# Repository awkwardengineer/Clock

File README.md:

# Intro
This is the repository for the AWK-105 Voltmeter clock. Here is where we'll be storing requirements documents, design history files, useful tidbits of information, and other material that otherwise wouldn't be release to manufacture or included in a Bill of Materials

##Consumer Facing Page
The repo may be cool, but it's not for everyone. The consumer facing product page has the bulk of the media material.

[Awkward Engineer Product Page](http://www.awkwardengineer.com/pages/voltmeter-clock)

##How This Repo Is Organized
In general, there are two categories of thing:  
+ Artifacts that will become part of the Bill Of Materials and will be released to a manufacturer. This includes CAD files, drawings, Gerbers, etc.  
+ Documentation and design files that record useful and important information, but that the manufacturer doesn't need to actually MAKE something.

The idea was to try to organize the documentation near the design file, kindof like things are arranged below.

Clock  
|  
|--Mechanical  
|&nbsp;&nbsp;&nbsp;|----CAD            <=== BOM artifacts, 3d part files, drawings  
|&nbsp;&nbsp;&nbsp;|----Design Docs    <=== Documentation specific to mechanical stuff
|&nbsp;&nbsp;&nbsp;|----Reference Mat. <=== Usually mostly .pdfs  
|  
|--Electrical  
|&nbsp;&nbsp;&nbsp;|----CAD            <=== Gerbers, net files, etc...  
|&nbsp;&nbsp;&nbsp;|----Design Docs    <=== Documentation specific to electrical stuff  
|  
|--Photos  
|  
|--etc...  

##Design Documents
Here are some quick links to some design stuff, right off the bat.

[Requirements](Electrical/Design Docs/requirements.md)  
[Microchip selection](Electrical/Design Docs/microcontroller selection.md)  
Sales strategy

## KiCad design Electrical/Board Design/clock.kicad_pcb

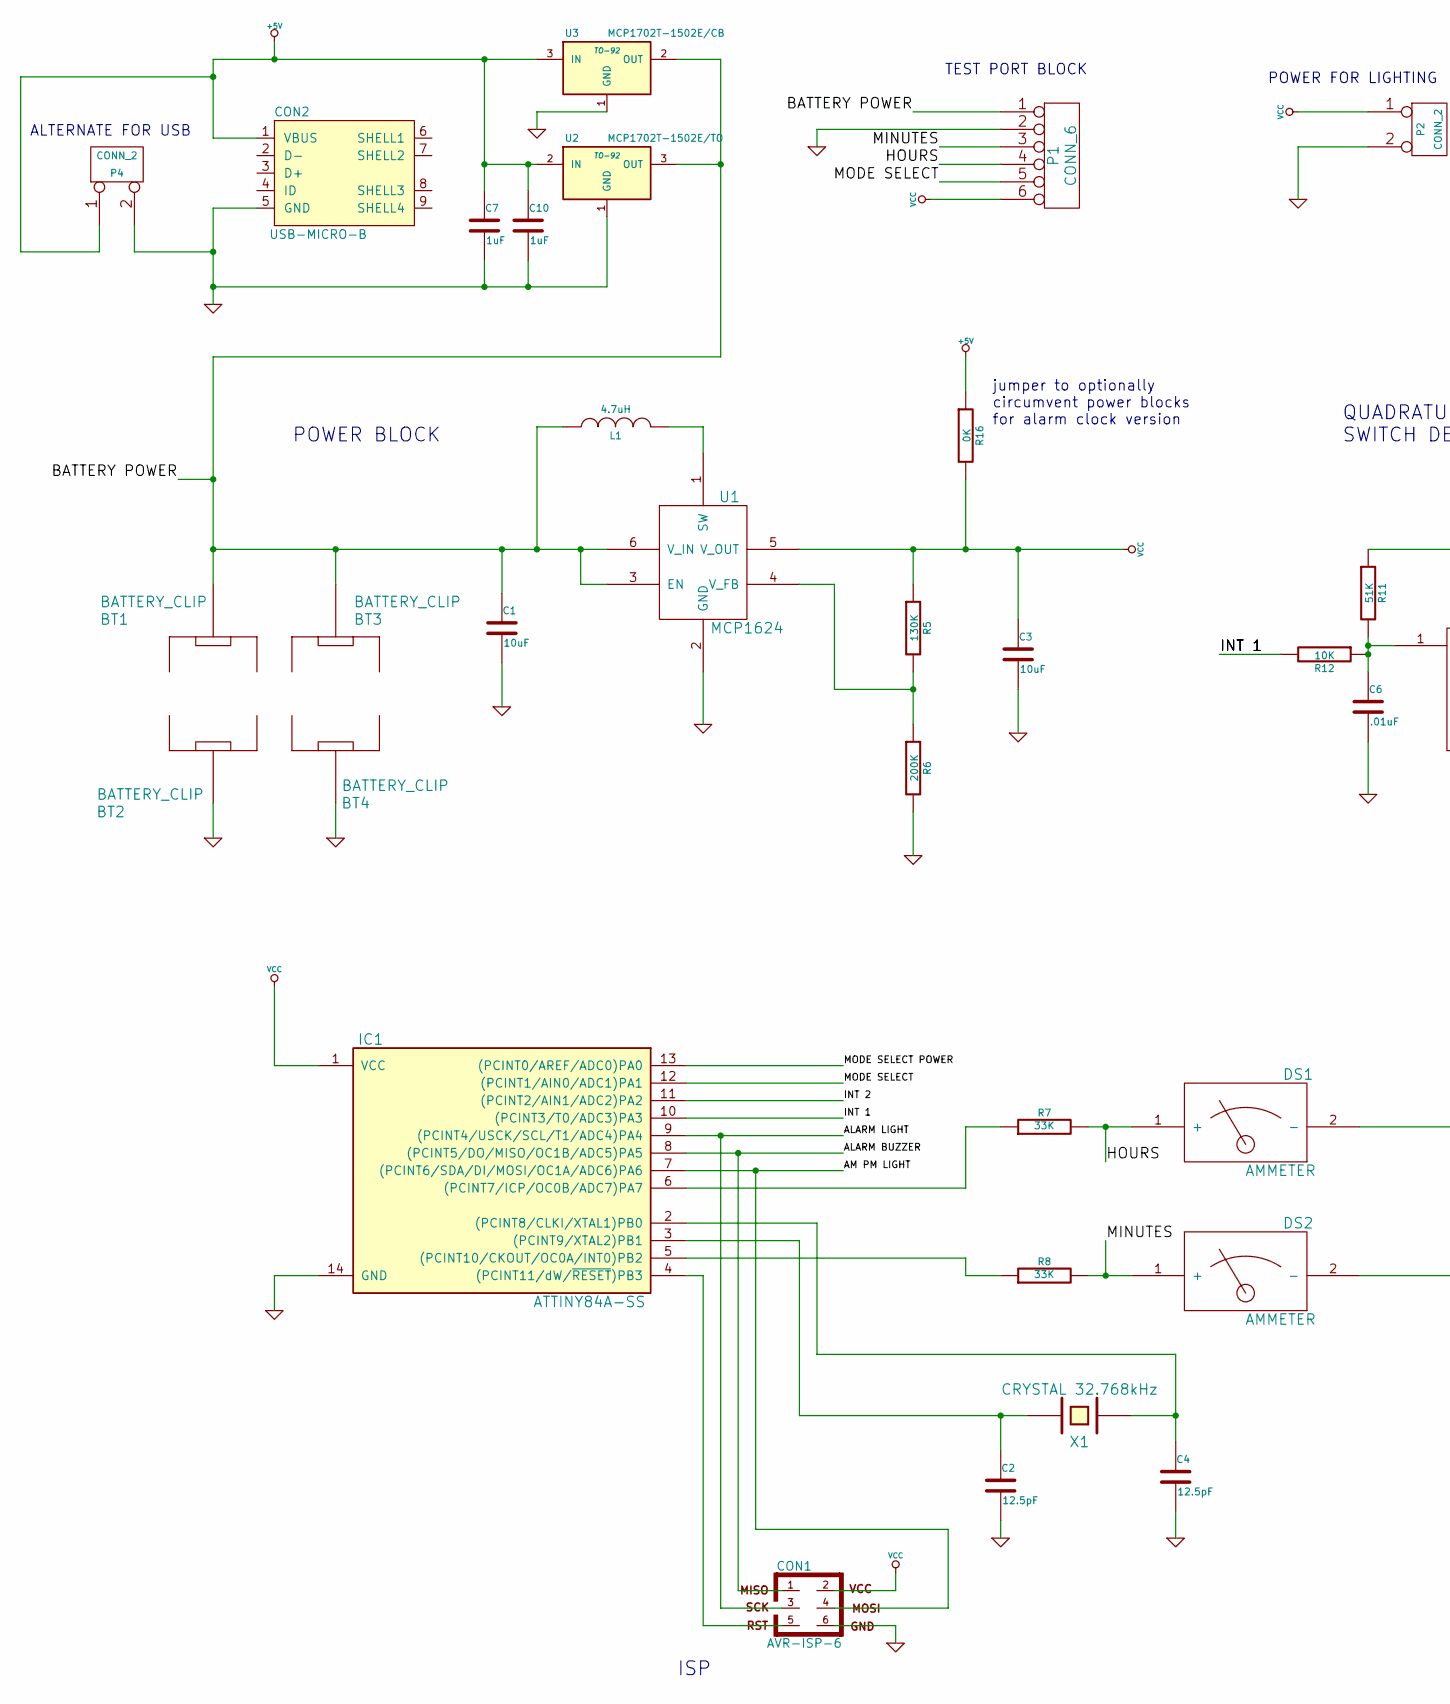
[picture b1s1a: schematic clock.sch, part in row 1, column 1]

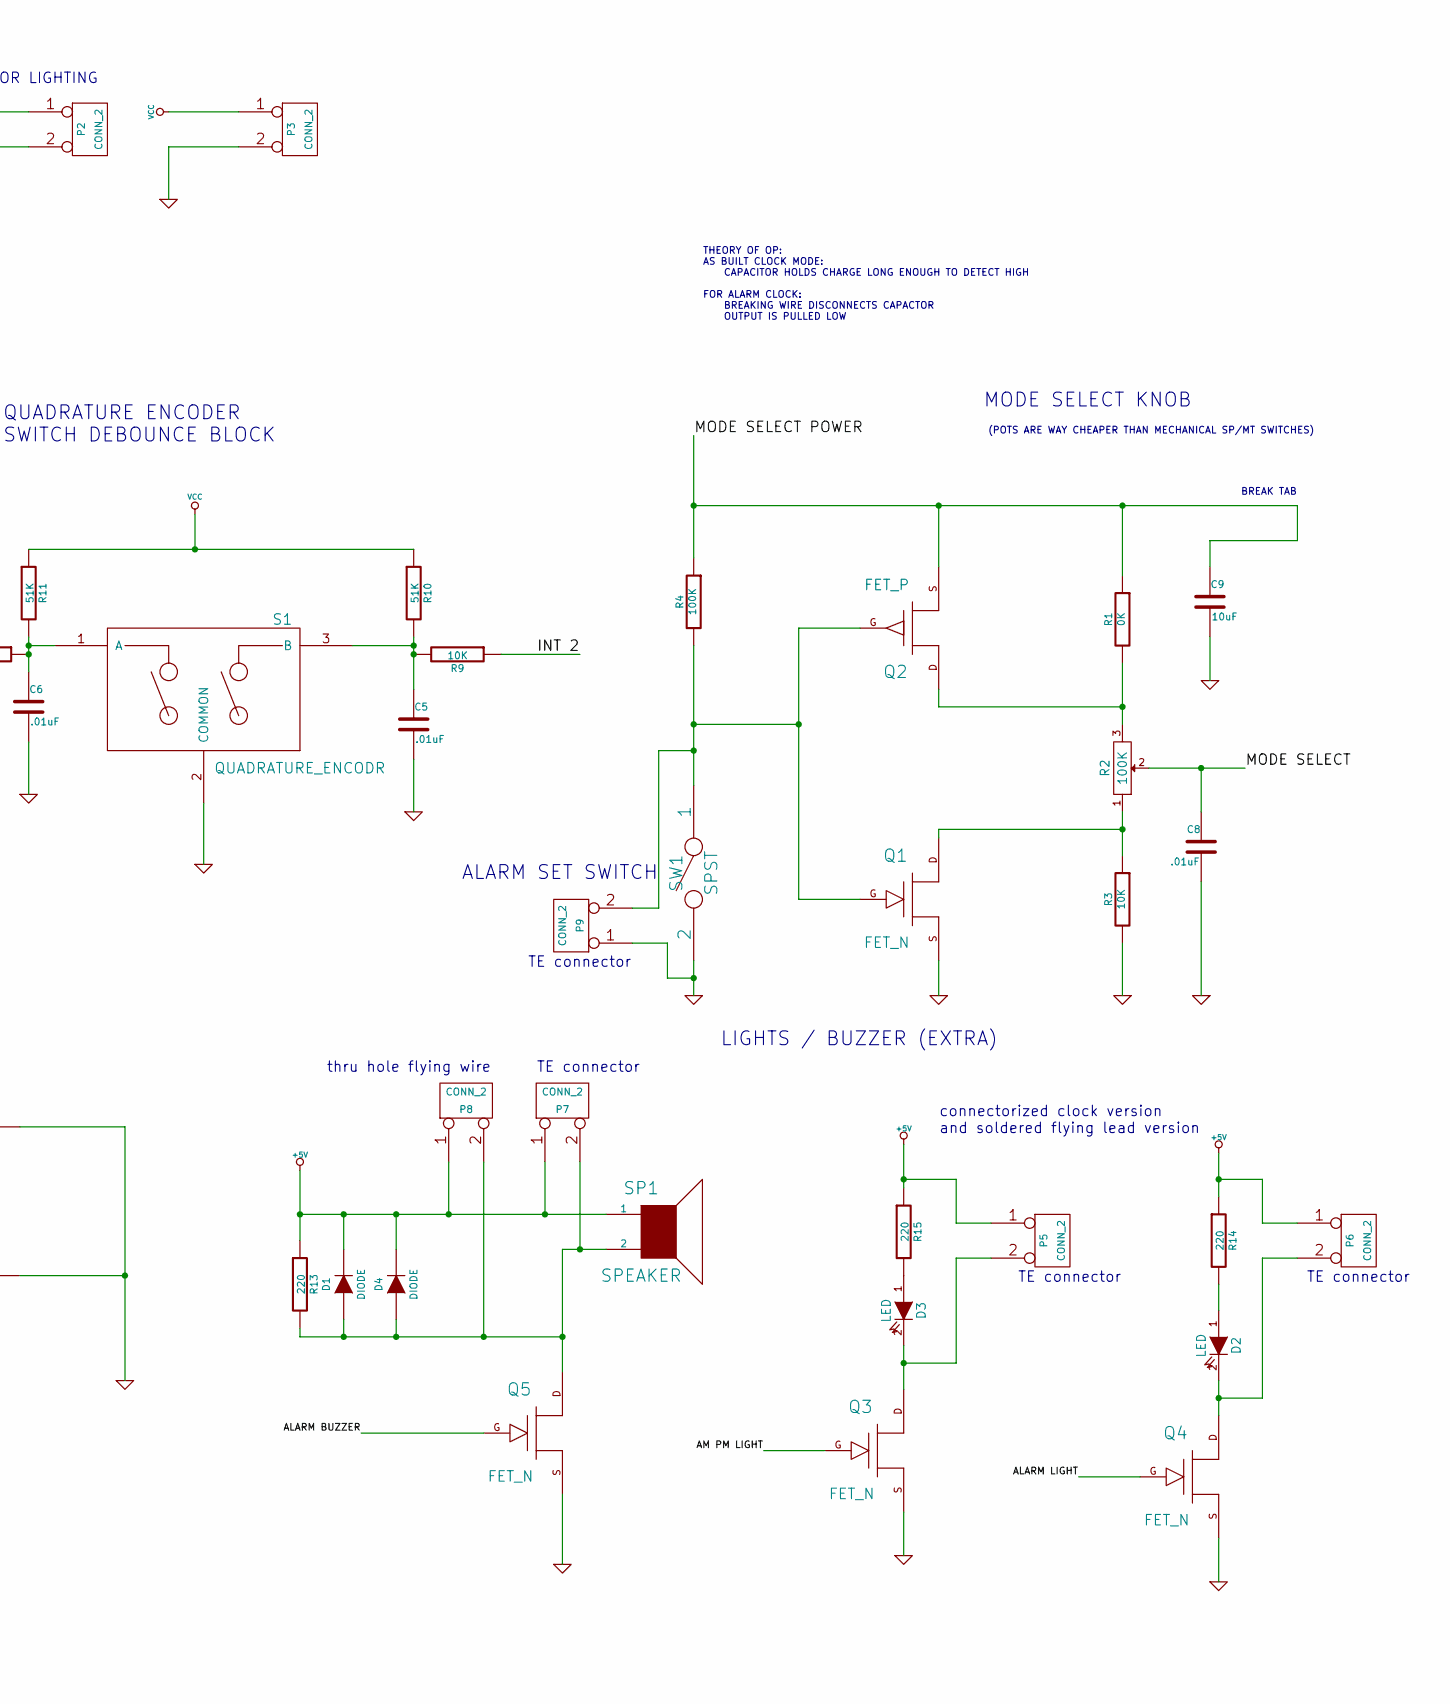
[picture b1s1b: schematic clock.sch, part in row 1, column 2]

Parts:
BT1, BT2, BT3, BT4: BATTERY_CLIP
C1, C3, C9: 10uF
C2, C4: 12.5pF
C5, C6, C8: .01uF
C7, C10: 1uF
CON1: AVR-ISP-6
CON2: USB-MICRO-B
D1, D4: DIODE
D2, D3: LED
DS1, DS2: AMMETER
IC1: ATTINY84A-SS; SO14
L1: 4.7uH
P1: CONN_6
P2, P3, P4, P5, P6, P7, P8, P9: CONN_2
Q1, Q3, Q4, Q5: FET_N
Q2: FET_P
R1, R16: 0K
R2, R4: 100K
R3, R9, R12: 10K
R5: 130K
R6: 200K
R7, R8: 33K
R10, R11: 51K
R13, R14, R15: 220
S1: QUADRATURE_ENCODR
SP1: SPEAKER
SW1: SPST
U1: MCP1624
U2: MCP1702T-1502E/TO; TO-92
U3: MCP1702T-1502E/CB; TO-92
X1: CRYSTAL 32.768kHz

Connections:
+5V: C7.1, C10.1, CON2.1 (VBUS), D1.2 (K), D4.2 (K), P4.1, P5.1, P6.1, P7.1, P8.1, R13.1, R14.1, R15.1, R16.1, SP1.1, U2.2 (IN), U3.3 (IN)
/ALARM BUZZER: CON1.1, IC1.8 ((PCINT5/DO/MISO/OC1B/ADC5)PA5), Q5.G
/ALARM LIGHT: CON1.3, IC1.9 ((PCINT4/USCK/SCL/T1/ADC4)PA4), Q4.G
/AM PM LIGHT: CON1.4, IC1.7 ((PCINT6/SDA/DI/MOSI/OC1A/ADC6)PA6), Q3.G
/BATTERY POWER: BT1.~, BT3.~, C1.1, L1.1, P1.1, U1.3 (EN), U1.6 (V_IN), U2.3 (OUT), U3.2 (OUT)
/HOURS: DS1.1 (+), P1.4, R7.2
/INT 1: IC1.10 ((PCINT3/T0/ADC3)PA3), R12.2
/INT 2: IC1.11 ((PCINT2/AIN1/ADC2)PA2), R9.1
/MINUTES: DS2.1 (+), P1.3, R8.2
/MODE SELECT: C8.1, IC1.12 ((PCINT1/AIN0/ADC1)PA1), P1.5, R2.2
/MODE SELECT POWER: C9.1, IC1.13 ((PCINT0/AREF/ADC0)PA0), Q2.S, R1.1, R4.1
GND: BT2.~, BT4.~, C1.2, C2.2, C3.2, C4.2, C5.2, C6.2, C7.2, C8.2, C9.2, C10.2, CON1.6, CON2.5 (GND), DS1.2 (-), DS2.2 (-), IC1.14 (GND), P1.2, P2.2 (PM), P3.2 (PM), P4.2 (PM), P9.1, Q1.S, Q3.S, Q4.S, Q5.S, R3.2, R6.2, S1.2 (COMMON), SW1.2, U1.2 (GND), U2.1 (GND), U3.1 (GND)
unnamed: R5.2, R6.1, U1.4 (V_FB)
unnamed: C5.1, R9.2, R10.2, S1.3 (B)
unnamed: IC1.5 ((PCINT10/CKOUT/OC0A/INT0)PB2), R8.1
unnamed: L1.2, U1.1 (SW)
unnamed: D1.1 (A), D4.1 (A), P7.2 (PM), P8.2 (PM), Q5.D, R13.2, SP1.2
unnamed: P9.2 (PM), Q1.G, Q2.G, R4.2, SW1.1
unnamed: Q1.D, R2.1, R3.1
unnamed: Q2.D, R1.2, R2.3
unnamed: D2.1 (A), R14.2
unnamed: IC1.6 ((PCINT7/ICP/OC0B/ADC7)PA7), R7.1
unnamed: C6.1, R11.2, R12.1, S1.1 (A)
unnamed: CON1.5, IC1.4 ((PCINT11/dW/~RESET~)PB3)
unnamed: D3.2 (K), P5.2 (PM), Q3.D
unnamed: D3.1 (A), R15.2
unnamed: D2.2 (K), P6.2 (PM), Q4.D
unnamed: C4.1, IC1.2 ((PCINT8/CLKI/XTAL1)PB0), X1.1
unnamed: C2.1, IC1.3 ((PCINT9/XTAL2)PB1), X1.2
VCC: C3.1, CON1.2, IC1.1 (VCC), P1.6, P2.1, P3.1, R5.1, R10.1, R11.1, R16.2, U1.5 (V_OUT)

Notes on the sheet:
QUADRATURE ENCODER SWITCH DEBOUNCE BLOCK
LIGHTS / BUZZER (EXTRA)
ISP
POWER BLOCK
TEST PORT BLOCK
POWER FOR LIGHTING
ALTERNATE FOR USB
jumper to optionally circumvent power blocks for alarm clock version
connectorized clock version and soldered flying lead version
ALARM SET SWITCH
(POTS ARE WAY CHEAPER THAN MECHANICAL SP/MT SWITCHES)
MODE SELECT KNOB
BREAK TAB
THEORY OF OP: AS BUILT CLOCK MODE: CAPACITOR HOLDS CHARGE LONG ENOUGH TO DETECT HIGH FOR ALARM CLOCK: BREAKING WIRE DISCONNECTS CAPACTOR OUTPUT IS PULLED LOW
thru hole flying wire
TE connector

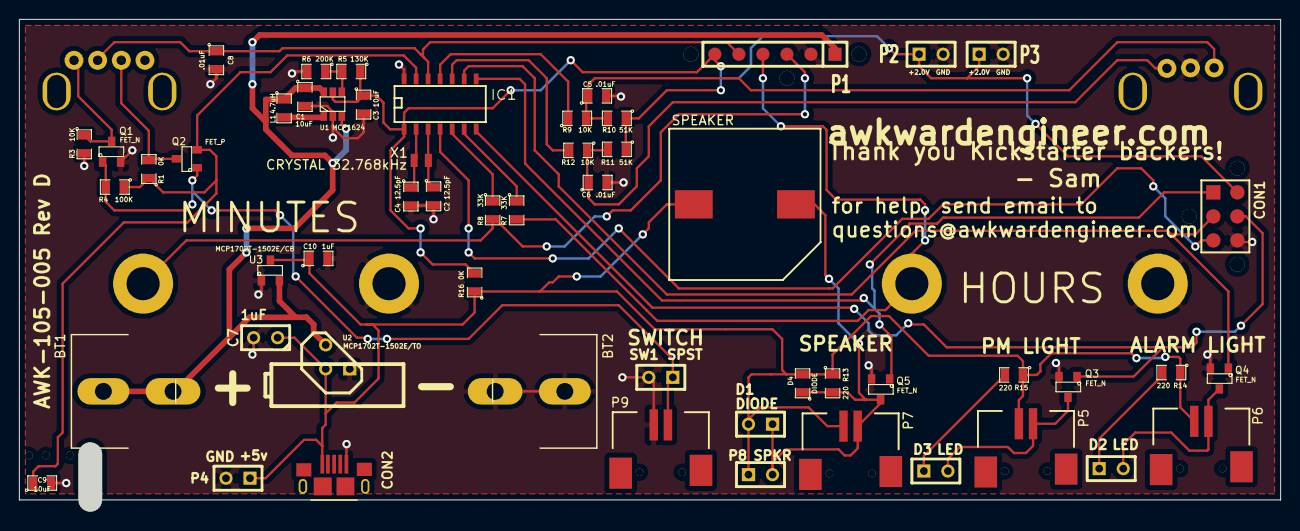
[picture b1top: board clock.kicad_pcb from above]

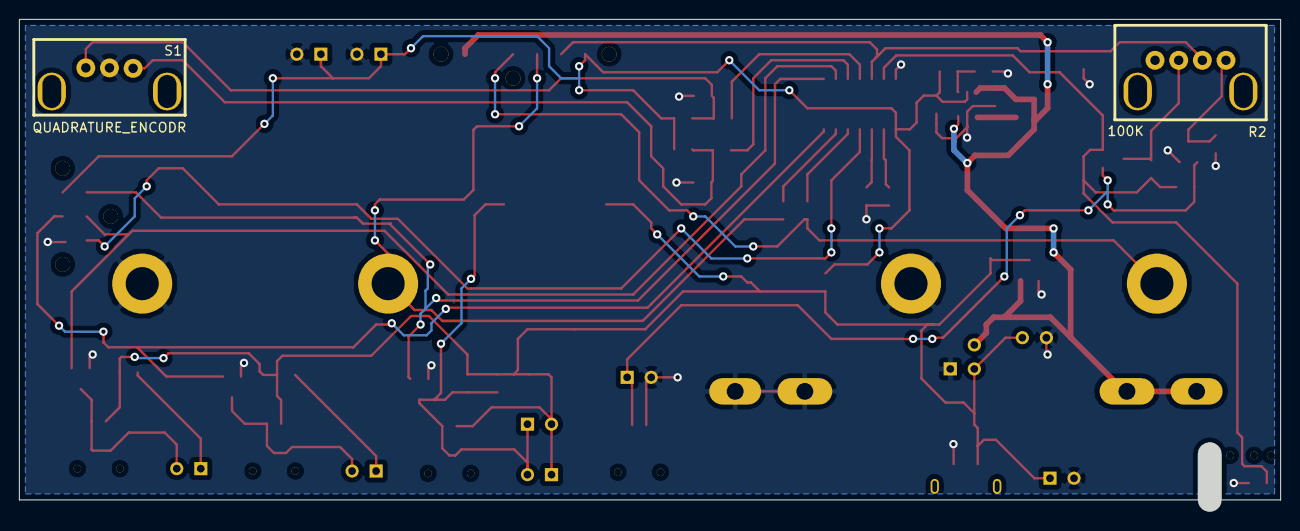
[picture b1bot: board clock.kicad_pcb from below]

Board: 2 copper layers, 130.9 x 49.6 mm, 62 parts (2 on the bottom side), 30 nets.

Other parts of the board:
BREAK_TAB: Val**; BREAK_HOLE
BREAK_TAB#2, BREAK_TAB#3: Val**; BREAK_HOLE

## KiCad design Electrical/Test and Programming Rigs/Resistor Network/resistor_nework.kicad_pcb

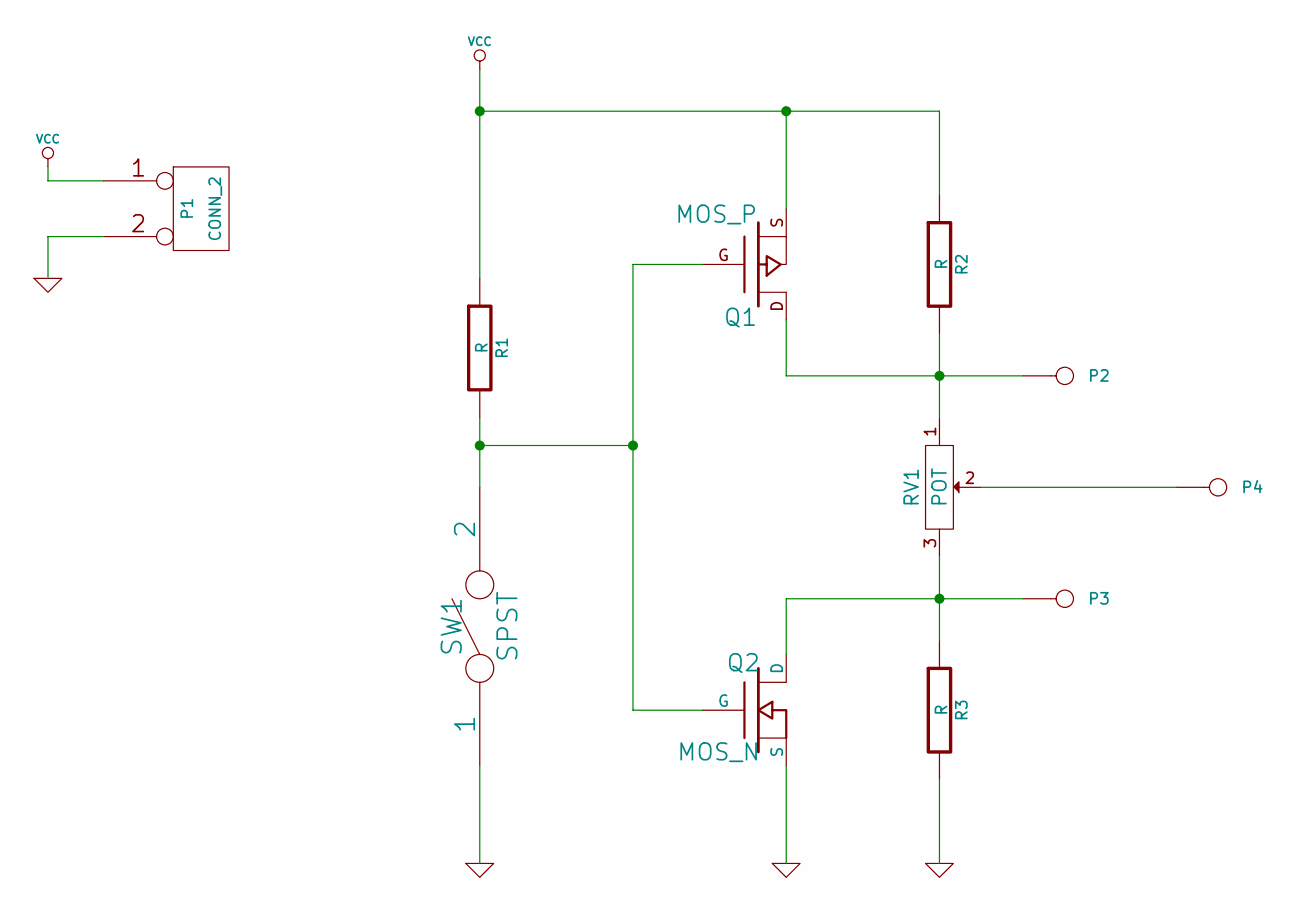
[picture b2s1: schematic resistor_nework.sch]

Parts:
P1: CONN_2
P2, P3, P4: CONN_1
Q1: MOS_P
Q2: MOS_N
R1, R2, R3: R
RV1: POT
SW1: SPST

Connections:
GND: P1.2 (PM), Q2.S, R3.2, SW1.1
unnamed: Q1.G, Q2.G, R1.2, SW1.2
unnamed: P4.1, RV1.2
unnamed: P3.1, Q2.D, R3.1, RV1.3
unnamed: P2.1, Q1.D, R2.2, RV1.1
VCC: P1.1, Q1.S, R1.1, R2.1

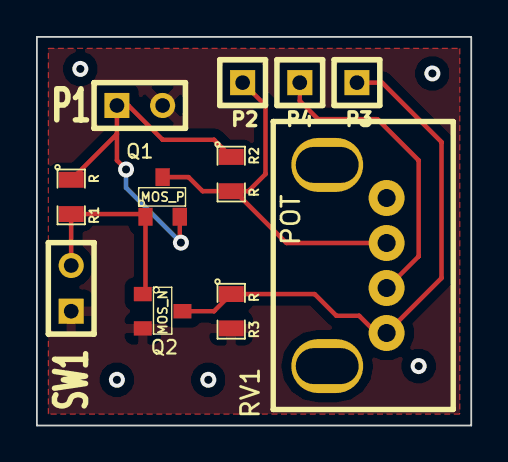
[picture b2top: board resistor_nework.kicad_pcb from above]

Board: 2 copper layers, 24.1 x 21.6 mm, 11 parts (0 on the bottom side), 6 nets.

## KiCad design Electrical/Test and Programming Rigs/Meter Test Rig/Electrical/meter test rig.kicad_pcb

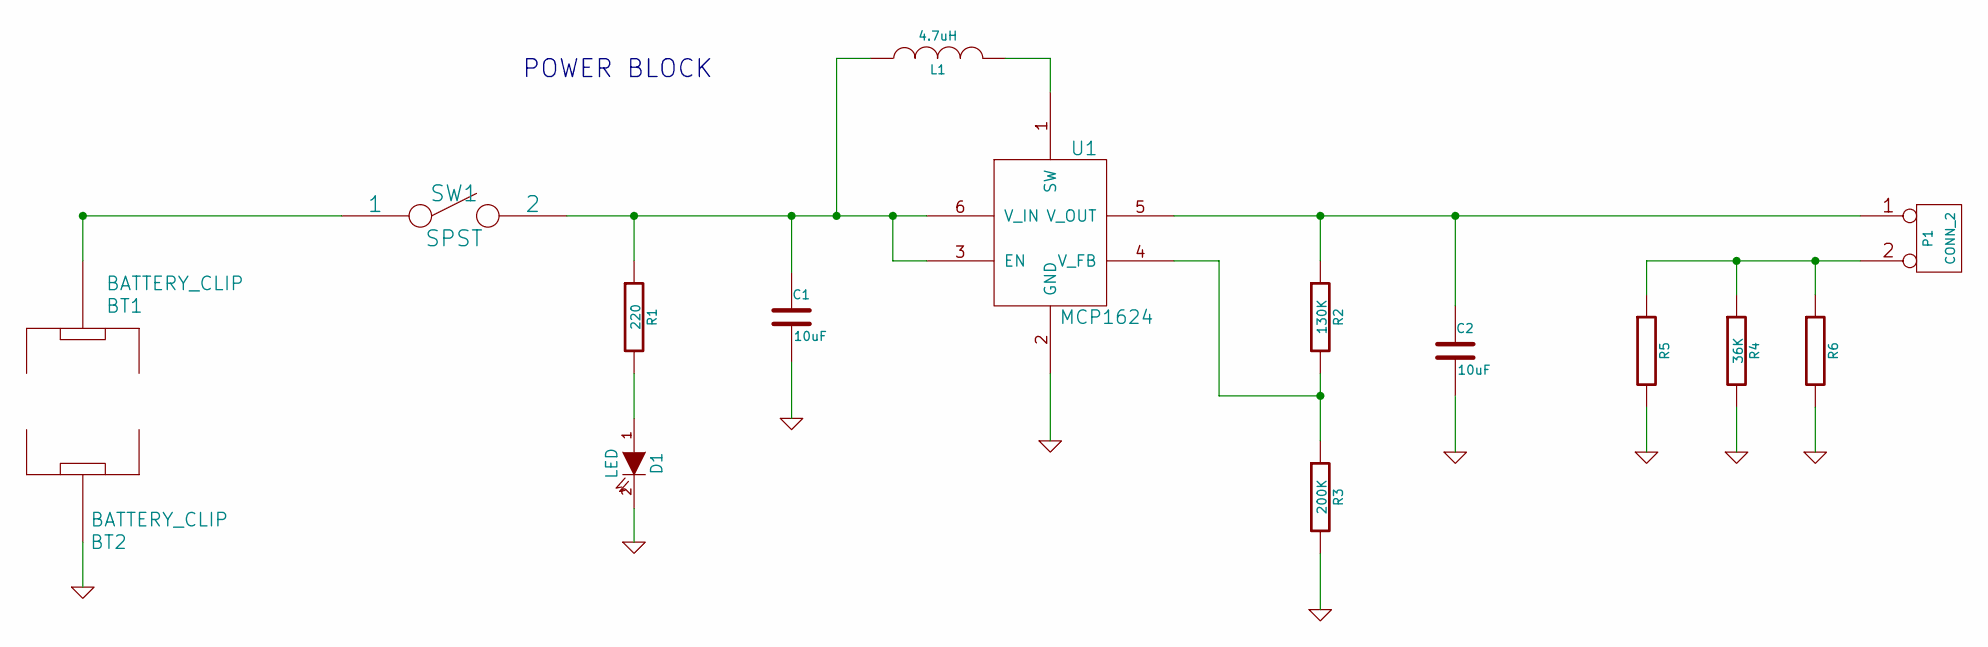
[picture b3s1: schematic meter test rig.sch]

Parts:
BT1, BT2: BATTERY_CLIP
C1, C2: 10uF
D1: LED
L1: 4.7uH
P1: CONN_2
R1: 220
R2: 130K
R3: 200K
R4: 36K
R5, R6: (no value)
SW1: SPST
U1: MCP1624

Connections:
GND: BT2.~, C1.2, C2.2, D1.2 (K), R3.2, R4.2, R5.2, R6.2, U1.2 (GND)
unnamed: D1.1 (A), R1.2
unnamed: L1.2, U1.1 (SW)
unnamed: P1.2 (PM), R4.1, R5.1, R6.1
unnamed: BT1.~, SW1.1
unnamed: C1.1, L1.1, R1.1, SW1.2, U1.3 (EN), U1.6 (V_IN)
unnamed: C2.1, P1.1, R2.1, U1.5 (V_OUT)
unnamed: R2.2, R3.1, U1.4 (V_FB)

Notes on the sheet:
POWER BLOCK

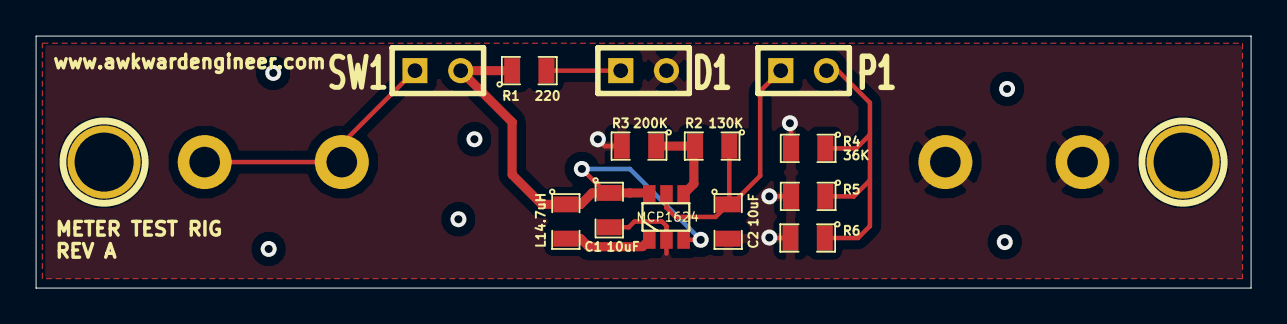
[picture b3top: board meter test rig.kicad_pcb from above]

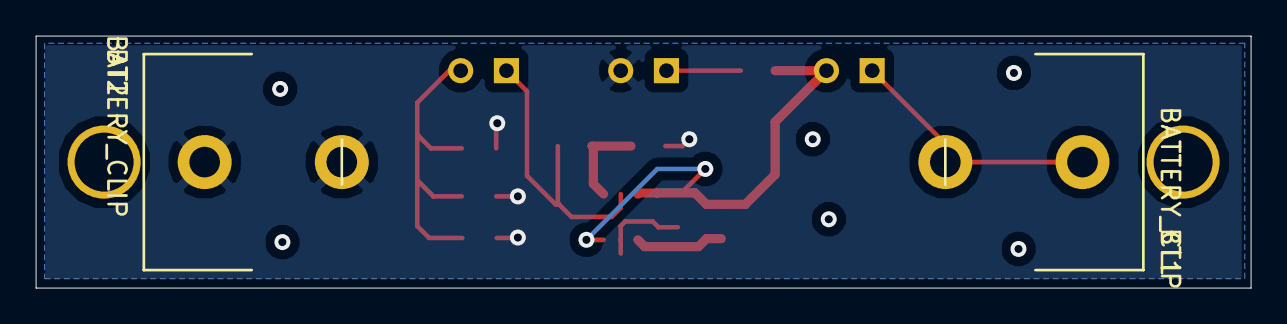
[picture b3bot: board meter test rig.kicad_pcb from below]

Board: 2 copper layers, 67.5 x 14.0 mm, 17 parts (2 on the bottom side), 8 nets.

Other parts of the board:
1PIN, 1PIN#2: P***; 1pin

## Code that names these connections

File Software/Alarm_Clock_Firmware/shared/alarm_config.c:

/*
 * alarm_config.c
 *
 * Created: 3/12/2016 8:36:20 PM
 *  Author: sfeller
 */ 

#ifndef _ALARM_CONFIG_C_
#define _ALARM_CONFIG_C_



//#include "alarm_config.h"
#include <avr/io.h>
#include <avr/interrupt.h>

 
 /**********************************
 * pinouts for ATtiny24/44/84 family
 ***********************************/
 
#define MODE_SELECT_POWER PA0
#define MODE_SELECT_INPUT PA1
#define QUAD_INT1 PA2
#define QUAD_INT2 PA3
#define MINUTES_OUT PA7
#define HOURS_OUT PB2
 
#define ALARM_LIGHT PA4
#define ALARM_BUZZER PA5
#define PM_LIGHT PA6

#define HOURS_PWM OCR0B
#define MINS_PWM OCR0A
  
 
 /**********************************
 * time related constants
 ***********************************/
 
#define F_CPU 32768 //default internal clock speed, actual speed will be changed to 32.768 clock crystal
#define TIMER_PRESCALER 1

//#define TIMER_TICKS_PER_INTERRUPT 32767
#define TIMER_TICKS_PER_INTERRUPT 8191  //4Hz interrupt rate
//#define TIMER_TICKS_PER_INTERRUPT 4095
#define TICKS_4HZ 8191
#define TICKS_2HZ 16383
#define TICKS_1HZ 32767

#define TWELVE_HOURS 43200 // 12hours * 60 min * 60 sec = 43200
#define TWENTY_FOUR_HOURS 86400
#define THIRTY_SIX_HOURS 129600 // 36 hours * 60 min * 60 sec - 129000 timer ticks
#define AMPM_LINE 86400 // 24 hrs * 60 min * 60 sec
#define FIVE_OCLOCK_SOMEWHERE 61200 //5pm in seconds
#define NINE_AM 118800// 9*60min*60sec + 86400 
//12 - 24 hrs is am
//24 - 36 hrs is pm


 // conversion = 32768hz / TIMER_PRESCALER / TIMER_TICKS_PER_INTERRUPT = 1 timer interrupts/sec

#define MINS_CONVERSION 60  //  1 timer_ints/sec * 60 secs/min = 60 timer_ints/minute
#define SECONDS_CONVERSION 1
 
#define INITIAL_HOURS_CAL 240
#define INITIAL_MINUTES_CAL 240
 
 
 /**********************************
 * constants for knob "mode" positions
 ***********************************/

#define CAP_SENSE_THRESHOLD 20
#define SWITCH_THRESHOLD 64
#define USB_POWER_THRESHOLD 128
/*
**************************
*the following were the original knob position settings from the plain
*AWK-105 clock. they are here for reference, but will need to be updated.
**************************
#define test_low 0
#define test_high 13

#define time_low 14
#define time_high 64

#define warble_low 65
#define warble_high 128

#define cal_hours_low 129
#define cal_hours_high 215

#define cal_minutes_low 216
#define cal_minutes_high 255
*/

#define POS_test 10
#define POS_minutes 45
#define POS_hours 97
#define POS_warble 173
#define POS_time 225
#define POS_alarm 255



#define CLOCK_POS_test 10
#define CLOCK_POS_minutes 65
#define CLOCK_POS_hours 129
#define CLOCK_POS_warble 216
#define CLOCK_POS_time 255







void indicator_init();
void pwm_init(void);
void timer_init(void);
void analog_init(void);
void pinchange_init(void);
void power_register_init(void);
void init_all(void);


void init_all(){
	indicator_init();
	pwm_init();
	timer_init();
	analog_init();
	pinchange_init();
	power_register_init();
	sei();
}

void indicator_init(){
	PORTA &= ~ (1 << ALARM_BUZZER)|(1 << ALARM_LIGHT)|(1 <<PM_LIGHT);	//disables pullup / turn outputs to zero when the DDRA is flipped
	DDRA |= (1 << ALARM_BUZZER)|(1 << ALARM_LIGHT)|(1 <<PM_LIGHT);		//switch pins from inputs to outputs
	
}

// initialize PWM
void pwm_init()
{
	// Timer/Counter Control  Register 0A
	//  SET WAVE GENERATION MODE
	//  ***********************************************************
	//  Setting WaveGenerationMode bits 00:02 to 0b001 puts the counter in phase correct PWM mode
	//  and sets the TOP of the counter to the full 0xFF range. (see page83 of docs)
	
	//  SET OUTPUT COMPARISON MODE
	//  ***********************************************************
	//  Setting only Compare Output Mode bit A1 (COM0A1) clears the counter when up-counting on a match and sets it
	//  when down-counting. Kinda like inverted mode. (See page 81/82).
	
	TCCR0A = (1<<WGM00)|(1<<COM0A1)|(1<<COM0B1); ;
	
	// SET CLOCK SOURCE
	// No Clock prescaler will be necessary for the PWM
	// System clock is at 32khz
	// 32khz / 256bits*2 for counting up AAAND down = 64Hz
	
	TCCR0B |= (1 << CS00); // set clock source to 0b001 for on with no prescaler
	
	//  SET DATA DIRECTION REGISTERS
	//  ***********************************************************
	// the Output Compare 0A register (OC0A) is PortB2, and OC0B is on PortA7
	// set the Data Direction Register
	DDRB |= (1<<HOURS_OUT);
	DDRA |= (1<<MINUTES_OUT);
}

void timer_init()
{
	// Connect LED to PA0 on pin 13
	// DDRA |= (1<<PA0);				//on the breadboard, there was an LED on this pin, but it has been removed on the PCB
	
	//  SET WAVE GENERATION MODE
	//  ***********************************************************
	// Timer/Conter Control Register 0A and 0B
	// Wave Generation Mode bit 13:10 need to be set to 0b1111
	// to put the timer in Fast PWM mode.
	// Sets the TOP of the register to OCR1A
	
	
	OCR1A = TIMER_TICKS_PER_INTERRUPT; // will trigger Timer1A every __ sec or so. 1A needs to be the larger number, as that does the actual Clear Timer on Compare
	OCR1B = TIMER_TICKS_PER_INTERRUPT + 1;
	
	TCCR1A |= (1<<WGM11)|(1<<WGM10);					//set WGM to 0b1111 for fastpwm with OCR1A as the top
	TCCR1B |= (1<<WGM13)|(1<<WGM12)|(1 << CS10);;		//set WGM to 0b1111 for fastpwm with OCR1A as the top
	// SET CLOCK SOURCE
	//CS10 Set Clock Source Bits CS12:10 to 0b001 to turn timer on with no prescaler

	// SET OUTPUT COMPARISON MODE
	// Compare Output Mode doesn't need to be set, the output pin is disconnected by default
	
	
	// ENABLE INTERRUPT
	// Output Compare A Match Interrupt Enable
	
	TIMSK1 |= (1 << TOIE1)|(1 << OCIE1B);;  // TOIE1 trigger interrupt when TIMER1 reaches the TOP of A
	// OCIE1B  trigger interrupt at halfway to top of A as well.
}

void analog_init(){
	
	//Voltage Reference is already set to Vcc by default (pg 145)
	
	// set PORTA1 (MODE_SELECT) as the input to the ADC (Pin #12) by setting MUX5:0 to 0b00001
	//ADC Multiplexer Selection Register
	ADMUX |= (1<<MUX0);
	
	//ADC Control and Status Register A
	ADCSRA |= (1<<ADEN)|(1<<ADPS0);; // ADEN enables the ADC
	//ADPS0 prescaler divides clock by 1, ADPS2:0 = 0b001
	
	//ADC Control and Status Register B
	ADCSRB |= (1 <<ADLAR); //left adjust result, so of the 10 bits, the high 8 bit register has the data I need.
	
	DDRA |= (1<<MODE_SELECT_POWER); //used to select the potentiometer as an output
	//PORTA &= ~(1<<MODE_SELECT_POWER); //turn power to potentiometer off
}

void pinchange_init(){
	
	// General Interrupt Mask Register
	GIMSK |= (1<<PCIE0);  //Pin Change Interrupt Enable 0, turns on interrupts for Pin Change bits 7:0
	
	//Pin Change Mask Register
	PCMSK0 |= (1<<QUAD_INT1)|(1<<QUAD_INT2);  //turns on Pin Change interupts on QUAD_INT1 and QUAD_INT2
}

void power_register_init(){
	
	//MCUCR: MCU Control Register
	
	MCUCR |= (1<<BODS)|(1<<SE)|(0<<SM1)|(0<<SM0);;
	
	//BODS disable brown out detector
	//SE sleep enable
	//SM1, SM0  - sleepmode select 0b00; will enter IDLE mode with CPU shut down
	
	//PRR: Power Reduction Register
	
	PRR |= (1<<PRUSI); // shuts down the USI clock
	
}

#endif

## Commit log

2014-01-05 Initital Creation
2014-01-05 test mode with fast sweeping hands works
2014-01-06 added calibration and set time modes to switch selector
2014-02-04 removed pot knob with quad encoder, reassigned pins
2014-02-04 operation works, but interrupt is not functioning yet.
2014-02-05 interrupts work now!
2014-03-26 organizing folders
2014-03-26 cleaning stuff up some more
2014-03-26 added google drive files
2014-03-26 added requirements docs
2014-03-26 clarifaction from out of context copy/paste job
2014-03-26 updating selection doc to be more coherent...
2014-03-27 added pinout diagram
2014-03-27 added proposed pinouts
2014-03-27 reorganizing repo
2014-03-27 organizing repo
2014-03-27 moved a bunch of stuff around again
2014-03-27 moved a bunch of photos again
2014-03-27 added block diagram
2014-03-27 added block diagram to requirements
2014-03-27 moved some mechanical files
2014-03-27 moved even more stuff
2014-03-27 cleaning up the archive
2014-03-29 started board layout
2014-03-30 started on schematic capture
2014-04-02 encoder selection images
2014-04-02 knob selection memo
2014-04-02 selected Bourns as the enc./pot. company
2014-04-03 added specific part numbers
2014-04-03 added a picture
2014-04-03 changed knob length
2014-04-03 component image
2014-04-03 added CAD check drawing
2014-04-03 pot/encoder literature
2014-04-03 CAD check files
2014-04-07 found some good reference data
2014-04-09 renamed a folder
2014-04-09 power source memo started
2014-04-09 renamed to .md format
2014-04-09 fixed table
2014-04-09 started board power memo
2014-04-10 regulator research
2014-04-11 added board power picture
2014-04-11 svg file for board power
2014-04-11 added pic
2014-04-22 started planning architecture
2014-04-22 first edition of blinkie
2014-04-22 now interrupt driven
2014-04-22 ignoring some of the files
2014-04-22 analog read added
2014-04-23 Pin Change Interrupts Work
2014-04-24 both PWM compare registers in inverting mode
2014-04-25 calibration modes and time display working!
2014-04-25 updated the face designs
2014-04-25 modified the faceplate
2014-04-25 some changes to blinkie
2014-04-25 this is confusing!
2014-05-07 new blog post image
2014-05-07 working on interrupt stuff, about to start branch
2014-05-13 interrupts work way better now
2014-05-13 update gitignore
2014-05-19 started into board layout
2014-06-24 big catchup
2014-06-24 updated ignore
2014-06-24 more ignore
2014-06-24 committing changes to accessory files
2014-06-24 Created artwork files for decals
2014-06-25 graphics updates
2014-06-25 made drawings
2014-07-09 board layout updates for battery stuff
2014-07-17 updates to board layout
2014-07-17 misc files
2014-07-17 gitignore update
2014-07-17 updated board layout
2014-07-22 checking board layout against knob parts
2014-11-13 catching up on a bunch of stuff
2014-11-16 updated BOM info
2014-12-02 release to quote
2014-12-02 mechanical BOM updates
2014-12-02 knob info
2014-12-02 prepping media files
2014-12-02 wrote script for video
2014-12-29 clock face design work
2014-12-29 campaign planning
2014-12-29 media planning
2014-12-29 media and design files and images
2015-01-02 alternate power source research
2015-01-02 mechanical design updates
2015-01-02 cleaning up artwork file folder
2015-01-03 made more media material
2015-01-04 added LDO to schematic and board
2015-01-09 saving some design memos
2015-01-22 meter updates, DFM updates
2015-01-27 backer updates and artwork changes
2015-01-27 archived an old knob selection memo
2015-01-27 reorganizing meter quote folder
2015-01-27 new knob selection memo
2015-01-27 digikey quote on non-stock item
2015-03-06 mechanical and BOM updates
2015-03-06 communication with meter factory
2015-03-06 pot and encoder sourcing
2015-03-06 artwork updates for sending to factory
2015-03-06 artwork release package
2015-03-06 plastic knob sourcing
2015-03-06 starting to make purchases
2015-03-06 kickstarter user requests
2015-03-06 updated ignore file
2015-03-06 gitignore update again
2015-03-23 schematic back in old version of kicad
2015-03-23 switching battery clips
2015-03-23 quotes on chip programming
2015-03-23 making a test rig
2015-03-23 meter factory communications
2015-03-23 meter factory PO
2015-03-23 test rig PO's
2015-03-23 production planning stuff
2015-03-23 mechanical model updates
2015-04-14 Update kickstarter special requests.txt
    backer request added
2015-04-25 mechanical updates
2015-04-25 electrical design updates
2015-04-25 meter sourcing stuff
2015-04-25 more meter sourcing
2015-04-25 firmware updates!
2015-05-18 board updates
2015-05-18 board footprint checks
2015-05-21 board firmware prior to changes
2015-05-27 holy cow getting chips burned!
2015-07-05 production planning updates
2015-07-05 release firmware
2015-07-05 production planning and purchases
2015-07-05 photos for backer updates
2015-07-05 getting cases ready for purchase
2015-07-05 working on artwork
2015-07-05 organizing artwork folder and making new artwork
2015-07-05 update board design with new footprint
2015-07-05 release board design
2015-07-05 updated CAD models
2015-07-05 assembly sequence plan
2015-07-05 random file
2015-07-05 deleted files cleanup
2015-08-24 added artwork
2015-08-24 changing / updating artwork
2015-08-24 adding a bunch of photos
2015-08-24 added reference material for alarm clock
2015-08-24 CAD updates
2015-08-24 more artwork organization
2015-08-24 mechanical reference for switch
2015-08-24 adding production process photos
2015-08-24 more photos
2015-08-24 added photos from paint shop
2015-10-11 created instruction sheet
2015-10-11 updated assembly procedure
2015-10-11 request for shorter threads
    closes issue #28
2015-10-14 updates to BOM to help build quote package
2015-10-14 created facebook ad content
2015-10-14 added lots of pictures
2015-10-14 marketing images
2015-10-14 added some instructions and drawings
2015-10-14 saving more pictures
2015-10-29 updated mechanical case drawings
2015-10-29 lots of photo and ad updates
2015-10-29 made a test circuit board for the resistor divider
2015-10-29 saved some circuit board updates
2015-10-29 deleted some backer report stuff
2015-10-29 more cleanup
2015-10-29 software for alarm clock
2015-10-29 big catchup commit
2015-10-29 ignore file update
2015-10-29 removed some files from repository
2015-10-30 fixed schematic
    closes issue #17
2015-10-30 add filter cap
    closed issue #15
2015-10-30 closes issue 19, shortable pullup
2015-11-01 changed breakaway to a capacitor solution
2015-11-01 foot print and schematic updates
    got the LED TE connector, SMT LDO, transistor for AM/PM lights
    footprints and schematic updated
2015-11-02 photos for blog post about low power
2015-11-02 resized pictures for a blog post
2015-11-04 saved meter photos
2015-11-04 added buzzer info
2015-11-04 made changes to speaker footprint
2015-11-05 updated test pad foot print and also some transistors
2015-11-09 added picture of moustache
2015-11-09 reorganized board layout, but haven't fully wired
2015-11-19 finalized changes and sent to fab
2015-11-29 recorded some coating and packing issues to send to patriot
2015-11-29 saving a quote
2015-11-29 blog post material
2015-11-29 store updates for out of stock stuff
2015-11-29 alarm clock photos
2015-12-17 added photos and revH drawing updates
2015-12-18 made meter test rig software
2015-12-18 made changes to leaflet insert
2016-01-06 created part numbers for tools, other items, etc...
2016-01-06 customer's launch button photos!
2016-01-06 photos to share of assembly process
2016-01-06 picture for meter communications
2016-01-06 soldering iron picture
2016-01-06 renamed picture of soldering iron
2016-03-07 created the electrical rig
2016-03-07 added for insert and for updated instruction set
2016-03-07 lots of photos added
2016-03-07 renamed a folder and lost info from it
2016-03-07 updated mechanical stuff and some cleanup
2016-03-07 picture for assembly directions
2016-03-07 added a bunch of reference info
2016-03-12 alarm clock is now at Atmel Studio 7
2016-03-14 config file created, light flash test made
2016-03-14 changed gitignore
2016-03-14 updated git ignore again
2016-03-14 still trying to commit ignore
2016-03-14 trying to fix ignore
2016-03-14 trying to remove files i'm trying to ignore
2016-03-14 another git ignore update
2016-03-14 updated git ignore....again
2016-03-14 cleaning repo, untracking make files
2016-03-14 ignoring makefules
2016-03-14 cleaning up repo
2016-03-23 working on software
2016-03-23 added a bunch of software stuff
2016-03-23 clean up, removed file
2016-03-23 mechanical updates mixed on this branch
2016-03-23 more mechanical on this branch
2016-03-23 updated gitignore (again)
2016-03-23 more ignore updates
2016-03-27 added a bunch of pictures
2016-03-27 renamed file, verified alarm clock works
2016-03-27 changed LED backlight power source, simplified POT, added LED dimming
2016-04-10 alarm clock core features work!
2016-04-11 more feedback features added to clock
2016-04-14 sweep control working now
2016-06-14 boot program detects clock or alarm clock
2016-06-14 added pictures
2016-06-17 possible Alarm Clock production candidate?
2016-06-22 i believe this came from a copy paste thing
2016-06-22 organizing released software files for release
